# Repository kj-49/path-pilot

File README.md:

## Path Pilot

__Path Pilot__ is a self-navigating robot built on an [AVR128DB28](https://www.microchip.com/en-us/product/avr128db28) microcontroller. It was developed as part of a project during my second year of Electrical Engineering.

## PCB
As an additional aspect of our project, our group had the opportunity to design and order a PCB for our circuit. This was our first exposure to PCB design, and since it wasn't a requirement for the project, we had to learn how to use PCB design software independently. [Here](https://github.com/kj-49/path-pilot/tree/main/pcb/path-pilot-pcb) is what we came up with.

#### Schematic

#### PCB Design

#### PCB Render

#### Final PCB

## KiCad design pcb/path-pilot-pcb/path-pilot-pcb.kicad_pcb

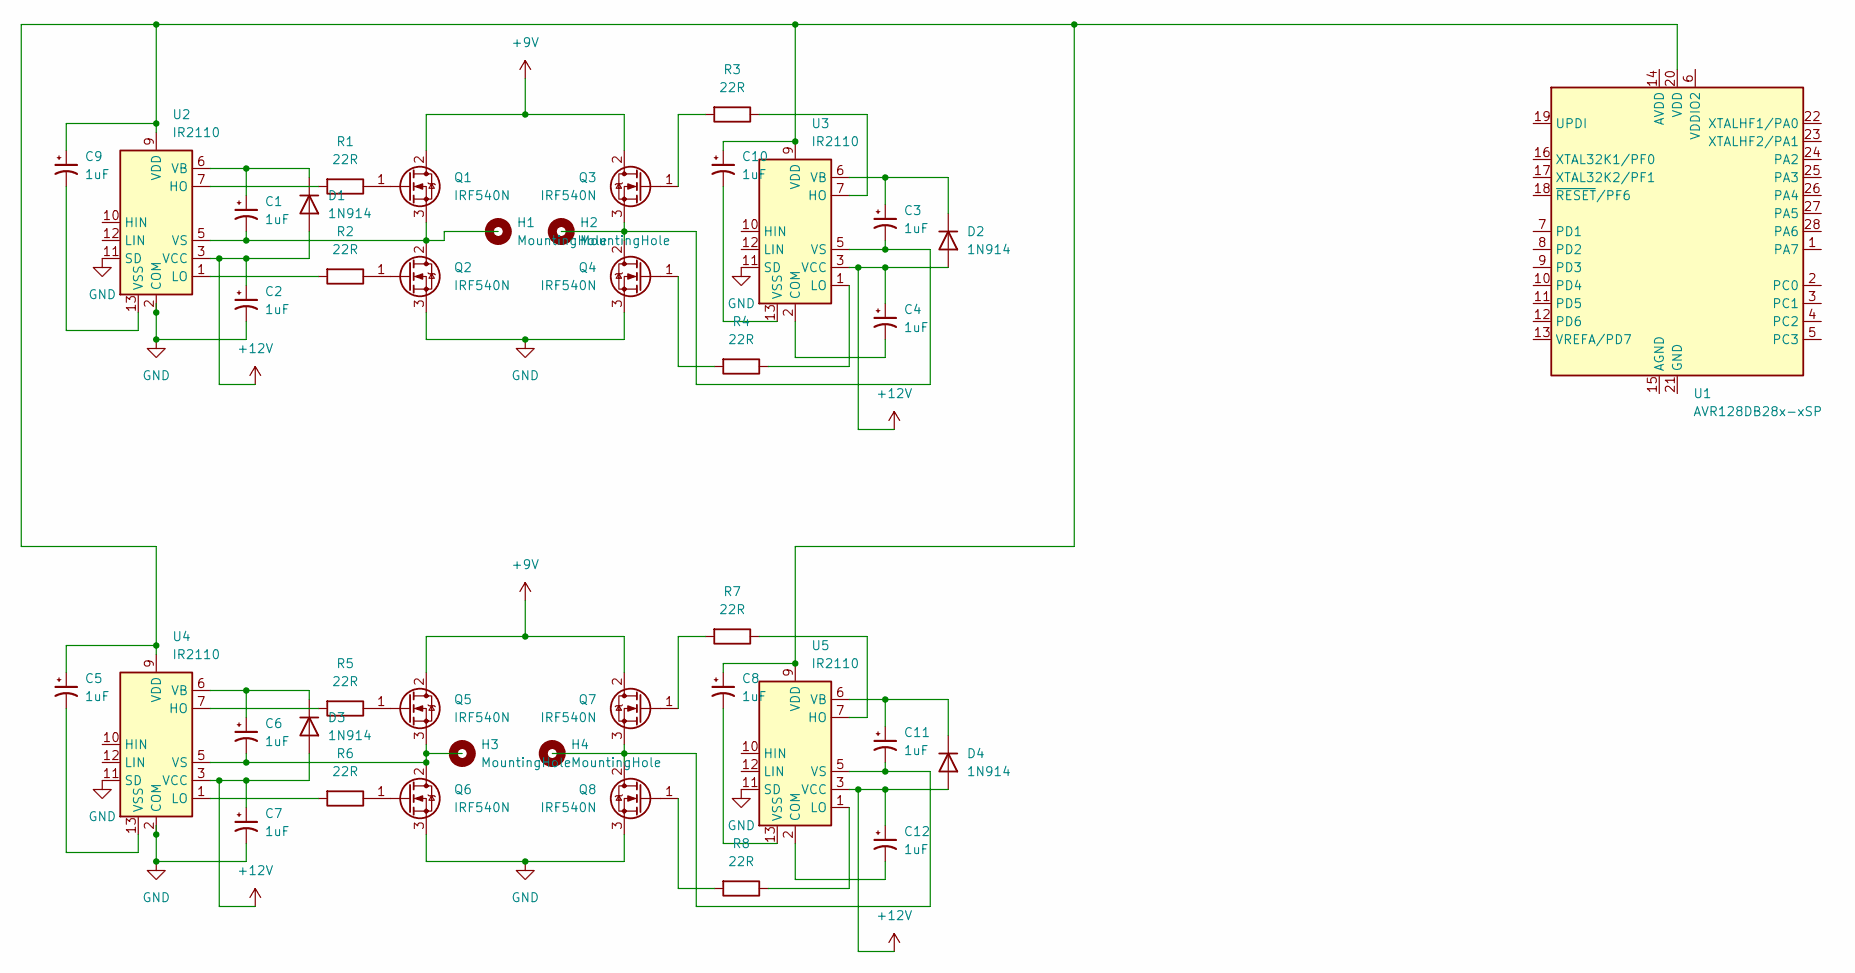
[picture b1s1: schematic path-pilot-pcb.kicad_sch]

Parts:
C1, C2, C3, C4, C5, C6, C7, C8, C9, C10, C11, C12: 1uF; R_Axial_DIN0204_L3.6mm_D1.6mm_P2.54mm_Vertical
D1, D2, D3, D4: 1N914; D_DO-35_SOD27_P7.62mm_Horizontal
H1, H2, H3, H4: MountingHole
Q1, Q2, Q3, Q4, Q5, Q6, Q7, Q8: IRF540N; TO-220-3_Vertical
R1, R2, R3, R4, R5, R6, R7, R8: 22R; R_Axial_DIN0204_L3.6mm_D1.6mm_P2.54mm_Vertical
U1: AVR128DB28x-xSP; DIP-28_W7.62mm
U2, U3, U4, U5: IR2110; DIP-14_W7.62mm

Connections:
+9V: Q1.2 (D), Q3.2 (D), Q5.2 (D), Q7.2 (D)
+12V: C2.1, C4.1, C7.1, C12.1, D1.2 (A), D2.2 (A), D3.2 (A), D4.2 (A), U2.3 (VCC), U3.3 (VCC), U4.3 (VCC), U5.3 (VCC)
GND: C2.2, C7.2, Q2.3 (S), Q4.3 (S), Q6.3 (S), Q8.3 (S), U2.2 (COM), U2.11 (SD), U3.11 (SD), U4.2 (COM), U4.11 (SD), U5.11 (SD)
unnamed: C1.1, D1.1 (K), U2.6 (VB)
unnamed: C3.1, D2.1 (K), U3.6 (VB)
unnamed: C6.1, D3.1 (K), U4.6 (VB)
unnamed: C11.1, D4.1 (K), U5.6 (VB)
unnamed: Q1.1 (G), R1.1
unnamed: C1.2, Q1.3 (S), Q2.2 (D), U2.5 (VS)
unnamed: Q2.1 (G), R2.1
unnamed: Q3.1 (G), R3.2
unnamed: C3.2, Q3.3 (S), Q4.2 (D), U3.5 (VS)
unnamed: Q4.1 (G), R4.2
unnamed: Q5.1 (G), R5.1
unnamed: C6.2, Q5.3 (S), Q6.2 (D), U4.5 (VS)
unnamed: Q6.1 (G), R6.1
unnamed: Q7.1 (G), R7.2
unnamed: C11.2, Q7.3 (S), Q8.2 (D), U5.5 (VS)
unnamed: Q8.1 (G), R8.2
unnamed: C5.1, C8.1, C9.1, C10.1, U1.20 (VDD), U2.9 (VDD), U3.9 (VDD), U4.9 (VDD), U5.9 (VDD)
unnamed: R1.2, U2.7 (HO)
unnamed: R2.2, U2.1 (LO)
unnamed: C9.2, U2.13 (VSS)
unnamed: C4.2, U3.2 (COM)
unnamed: R3.1, U3.7 (HO)
unnamed: R4.1, U3.1 (LO)
unnamed: C10.2, U3.13 (VSS)
unnamed: R5.2, U4.7 (HO)
unnamed: R6.2, U4.1 (LO)
unnamed: C5.2, U4.13 (VSS)
unnamed: C12.2, U5.2 (COM)
unnamed: R7.1, U5.7 (HO)
unnamed: R8.1, U5.1 (LO)
unnamed: C8.2, U5.13 (VSS)

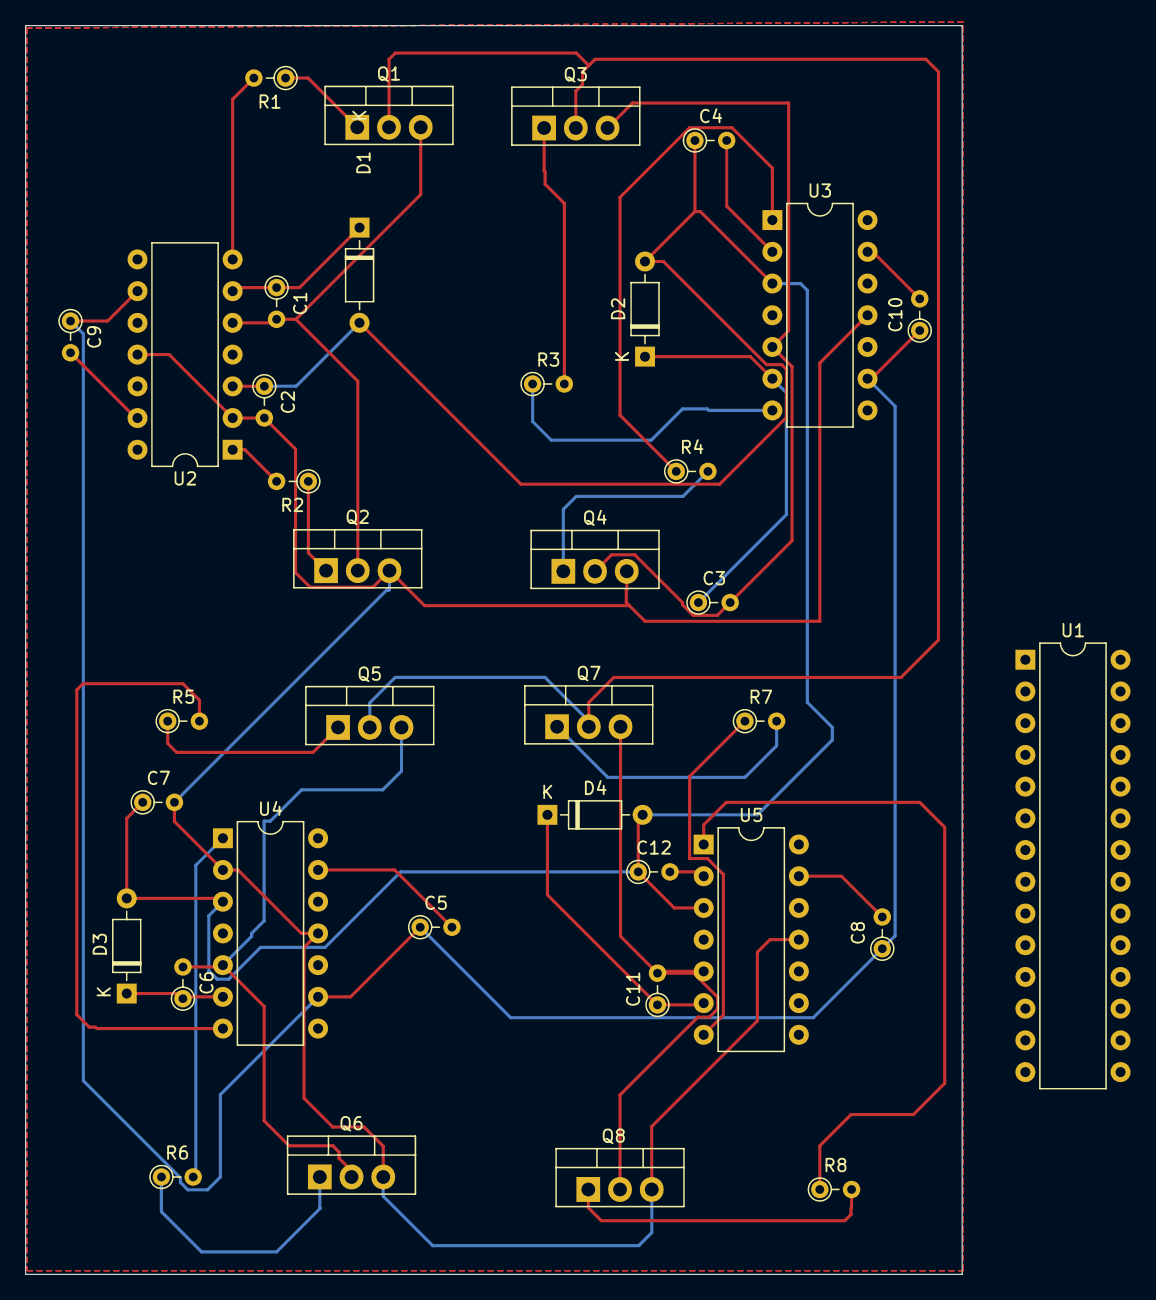
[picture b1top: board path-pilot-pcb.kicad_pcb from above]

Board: 2 copper layers, 75.0 x 100.0 mm, 37 parts (0 on the bottom side), 34 nets.

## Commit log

2024-02-02 project structure layed out
2024-02-03 Bit shifting now used and LED setting implemented
2024-02-04 work done on timing and ultrasonic sensor
2024-02-04 ultra-sonic sensor fully functional and outputting centimeters.
2024-02-04 obstruction function working, and formatting + naming changed.
2024-02-04 flicker added
2024-02-05 USART added by untested. Circuit diagram included
2024-02-06 Distance sensing bug fixed. Needed to reset timer every time we checked distance,
2024-02-06 Left testing code in last commit
2024-02-16 End of Feb16 Lab Session.
2024-02-16 Fixed naming in sensors.h
2024-02-23 Usart working
2024-03-01 pin changes for hbridge IC
2024-03-04 PWN started, not tested.
2024-03-05 Added frequency functionality to pwm. Untested.
2024-03-08 fixed bud where pin didnt't match port.
2024-03-10 pin config graphic, pwm fixes
2024-03-10 Spelling bug
2024-03-10 Debounce added to lessen metastability. Pin configuration fixed where PORTA would be set for PORTD.
2024-03-10 tuning for metastability good. Implemented gap between stopping threshold and moving threshold. This lesses the amount of flickering between states.
2024-03-12 Motor logic tested and working. Spinning and forward movement working
2024-03-15 prototype working a responding to objects
2024-03-15 Deleted vs files
2024-03-22 started, not working
2024-03-30 4 timer PWM implemented, not tested
2024-04-02 work done using PORT_t pointers
2024-04-02 Fixed enable bug. All PWM working except TCD
2024-04-02 Changed stopping and direction_t enum
2024-04-02 TCD conifuration bugs fixed
2024-04-02 PWM working on all 4 timers with consistent frequencies.
2024-04-03 Fixed type in comment
2024-04-03 Fixed pin diagram
2024-04-04 Refactoring & seperated duty cycle functionality
2024-04-04 fixed timer bug
2024-04-05 reverse + buzzer functional
2024-04-05 some more refactoring and abstractions
2024-04-05 H-bridge working & code tested
2024-04-09 Final Demo code
2024-04-12 Fixed MCU graphic in avr-common.h
2024-09-30 Modified folder structure and added circuit schematics.
2024-09-30 Cleaned up files and removed unused files.
2024-10-11 Added images
2024-10-11 Added PCB section to README
2024-10-11 Added README.md (#1)
    * Create README.md
    * Added PCB section to README
2024-10-11 Fixed paths in README.md
2024-12-09 Rename source code folder
